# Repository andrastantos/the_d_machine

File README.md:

# tcomp
A transistor-based computer

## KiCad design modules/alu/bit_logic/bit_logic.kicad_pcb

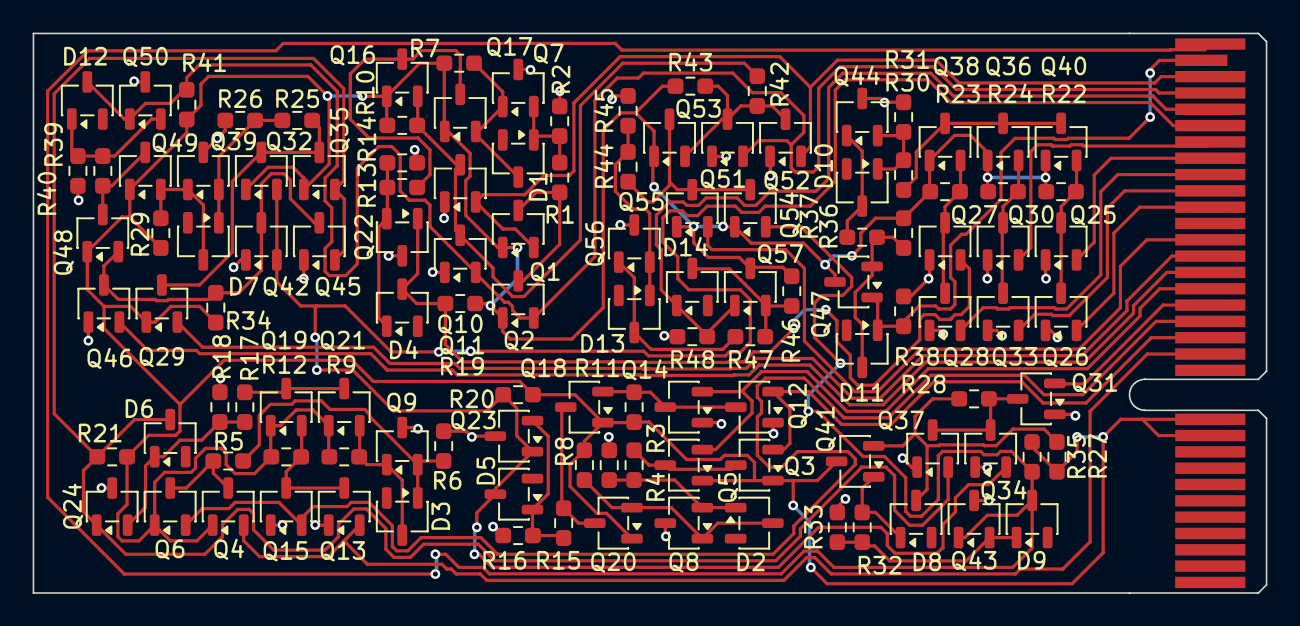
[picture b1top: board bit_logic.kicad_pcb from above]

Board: 2 copper layers, 75.6 x 34.3 mm, 120 parts (0 on the bottom side), 63 nets.

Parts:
D1, D2, D3, D4, D5, D6, D7, D8, D9, D10, D11, D12, D13, D14: BAT54LT1G; SOT-23-3
J1: PCIe_4x_edge; BUS_PCIexpress_x4
Q1, Q2, Q3, Q4, Q5, Q6, Q7, Q8, Q9, Q16, Q17, Q18, Q19, Q20, Q21, Q22, Q23, Q24, Q29, Q32, Q35, Q36, Q38, Q39, Q40, Q43, Q44, Q48, Q49, Q50, Q53, Q54, Q55, Q56: 2N3904; SOT-23-3
Q10, Q11, Q12, Q13, Q14, Q15, Q25, Q26, Q27, Q28, Q30, Q31, Q33, Q34, Q37, Q41, Q42, Q45, Q46, Q47, Q51, Q52, Q57: 2N3906; SOT-23-3
R1, R2, R3, R4, R5, R6, R13, R14, R15, R16, R17, R18, R25, R26, R27, R28, R30, R31, R39, R40, R44, R45: 220; R_0603_1608Metric_Pad0.98x0.95mm_HandSolder
R7, R8, R9, R19, R20, R21, R29, R32, R33, R35, R36, R37, R38, R41, R46, R47, R48: 100; R_0603_1608Metric_Pad0.98x0.95mm_HandSolder
R10, R11, R12, R22, R23, R24, R34, R43: 520; R_0603_1608Metric_Pad0.98x0.95mm_HandSolder
R42: 0; R_0603_1608Metric_Pad0.98x0.95mm_HandSolder

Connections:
/IN_A: J1.B14 (Pin_b14), Q3.2 (B), Q12.2 (B)
/IN_ADD_EN: J1.B24 (Pin_b24), Q28.2 (B)
/IN_AND_EN: J1.B19 (Pin_b19), Q29.2 (B)
/IN_A_NEXT: J1.B26 (Pin_b26), Q30.2 (B)
/IN_A_PREV: J1.B25 (Pin_b25), Q25.2 (B)
/IN_B: J1.B13 (Pin_b13), Q4.2 (B), Q13.2 (B)
/IN_C: J1.B30 (Pin_b30), Q1.2 (B), Q10.2 (B), Q52.2 (B)
/IN_C_IS_1: J1.B20 (Pin_b20), Q55.2 (B)
/IN_INV_A: J1.B17 (Pin_b17), Q5.2 (B), Q14.2 (B)
/IN_INV_B: J1.B15 (Pin_b15), Q6.2 (B), Q15.2 (B)
/IN_ROL_EN: J1.B22 (Pin_b22), Q26.2 (B)
/IN_ROR_EN: J1.B23 (Pin_b23), Q33.2 (B)
/OUT_A: D5.3 (K), J1.B27 (Pin_b27), Q23.1 (C), Q32.2 (B), Q34.2 (B), Q42.2 (B), R20.2
/OUT_C: D14.1 (A), J1.B28 (Pin_b28), Q57.1 (C), R48.1
/OUT_G: D9.3 (K), J1.B32 (Pin_b32), Q43.1 (C), Q54.2 (B), R35.2
/OUT_P: D12.3 (K), J1.B29 (Pin_b29), Q2.2 (B), Q11.2 (B), Q50.1 (C), Q51.2 (B), R41.2
/OUT_S: D11.1 (A), J1.B31 (Pin_b31), Q47.1 (C), R38.1
/XX: Q10.3 (E), Q11.3 (E), Q16.2 (B), R10.2, R42.1
/~IN_C_IS_0: J1.B16 (Pin_b16), Q31.2 (B)
/~IN_OR_EN: J1.B18 (Pin_b18), Q46.2 (B)
GND: J1.A10 (Pin_a10), J1.A11 (Pin_a11), J1.A12 (Pin_a12), J1.A13 (Pin_a13), J1.A14 (Pin_a14), J1.A15 (Pin_a15), J1.A16 (Pin_a16), J1.A17 (Pin_a17), J1.A18 (Pin_a18), J1.A19 (Pin_a19), J1.A20 (Pin_a20), J1.A21 (Pin_a21), J1.A22 (Pin_a22), J1.A23 (Pin_a23), J1.A24 (Pin_a24), J1.A25 (Pin_a25), J1.A26 (Pin_a26), J1.A27 (Pin_a27), J1.A28 (Pin_a28), J1.A29 (Pin_a29), J1.A30 (Pin_a30), J1.A31 (Pin_a31), J1.A32 (Pin_a32), Q7.3 (E), Q8.3 (E), Q9.3 (E), Q10.1 (C), Q11.1 (C), Q12.1 (C), Q13.1 (C), Q14.1 (C), Q15.1 (C), Q22.3 (E), Q23.3 (E), Q24.3 (E), Q25.1 (C), Q26.1 (C), Q27.1 (C), Q28.1 (C), Q30.1 (C), Q31.1 (C), Q33.1 (C), Q34.1 (C), Q37.1 (C), Q39.3 (E), Q42.1 (C), Q43.3 (E), Q44.3 (E), Q45.1 (C), Q46.1 (C), Q50.3 (E), Q51.1 (C), Q52.1 (C), Q56.3 (E), R2.2, R4.2, R6.2, R14.2, R16.2, R18.2, R26.2, R31.2, R33.2, R38.2, R40.2, R45.2, R48.2
unnamed: D1.1 (A), Q7.2 (B), R1.2, R2.1
unnamed: D1.3 (K), Q7.1 (C), Q17.2 (B), R7.2
unnamed: D2.1 (A), Q8.2 (B), R3.2, R4.1
unnamed: D2.3 (K), Q8.1 (C), Q20.2 (B), R8.2
unnamed: D3.1 (A), Q9.2 (B), R5.2, R6.1
unnamed: D3.3 (K), Q9.1 (C), Q21.2 (B), R9.2
unnamed: D4.1 (A), Q22.2 (B), R13.2, R14.1
unnamed: D4.3 (K), Q22.1 (C), Q27.2 (B), R19.2
unnamed: D5.1 (A), Q23.2 (B), R15.2, R16.1
unnamed: D6.1 (A), Q24.2 (B), R17.2, R18.1
unnamed: D6.3 (K), Q24.1 (C), Q35.2 (B), Q37.2 (B), Q45.2 (B), R21.2
unnamed: D7.1 (A), Q39.2 (B), R25.2, R26.1
unnamed: D7.3 (K), Q39.1 (C), Q49.2 (B), R29.2
unnamed: D8.1 (A), Q41.1 (C), R32.1
unnamed: D8.3 (K), Q41.2 (B), R27.2, R28.1
unnamed: D9.1 (A), Q43.2 (B), R32.2, R33.1
unnamed: D10.1 (A), Q44.2 (B), R30.2, R31.1
unnamed: D10.3 (K), Q44.1 (C), R37.2
unnamed: D11.3 (K), Q47.2 (B), R36.2, R37.1
unnamed: D12.1 (A), Q50.2 (B), R39.2, R40.1
unnamed: D13.1 (A), Q56.2 (B), R44.2, R45.1
unnamed: D13.3 (K), Q56.1 (C), R47.2
unnamed: D14.3 (K), Q57.2 (B), R46.2, R47.1
unnamed: Q1.3 (E), Q2.3 (E), R1.1
unnamed: Q3.3 (E), Q5.3 (E), R3.1
unnamed: Q4.3 (E), Q6.3 (E), R5.1
unnamed: Q12.3 (E), Q14.3 (E), Q18.2 (B), R11.2
unnamed: Q13.3 (E), Q15.3 (E), Q19.2 (B), R12.2
unnamed: Q16.3 (E), Q17.3 (E), R13.1
unnamed: Q18.3 (E), Q20.3 (E), R15.1
unnamed: Q19.3 (E), Q21.3 (E), R17.1
unnamed: Q25.3 (E), Q26.3 (E), Q40.2 (B), R22.2
unnamed: Q27.3 (E), Q28.3 (E), Q38.2 (B), R23.2
unnamed: Q29.3 (E), Q32.3 (E), Q35.3 (E), R25.1
unnamed: Q30.3 (E), Q33.3 (E), Q36.2 (B), R24.2
unnamed: Q31.3 (E), Q34.3 (E), Q37.3 (E), R28.2
unnamed: Q36.3 (E), Q38.3 (E), Q40.3 (E), R30.1
unnamed: Q42.3 (E), Q45.3 (E), Q46.3 (E), Q48.2 (B), R34.2
unnamed: Q48.3 (E), Q49.3 (E), R39.1
unnamed: Q51.3 (E), Q52.3 (E), Q53.2 (B), R42.2, R43.2
unnamed: Q53.3 (E), Q54.3 (E), Q55.3 (E), R44.1
VCC: J1.B10 (Pin_b10), J1.B11 (Pin_b11), Q1.1 (C), Q2.1 (C), Q3.1 (C), Q4.1 (C), Q5.1 (C), Q6.1 (C), Q16.1 (C), Q17.1 (C), Q18.1 (C), Q19.1 (C), Q20.1 (C), Q21.1 (C), Q29.1 (C), Q32.1 (C), Q35.1 (C), Q36.1 (C), Q38.1 (C), Q40.1 (C), Q41.3 (E), Q47.3 (E), Q48.1 (C), Q49.1 (C), Q53.1 (C), Q54.1 (C), Q55.1 (C), Q57.3 (E), R7.1, R8.1, R9.1, R10.1, R11.1, R12.1, R19.1, R20.1, R21.1, R22.1, R23.1, R24.1, R27.1, R29.1, R34.1, R35.1, R36.1, R41.1, R43.1, R46.1

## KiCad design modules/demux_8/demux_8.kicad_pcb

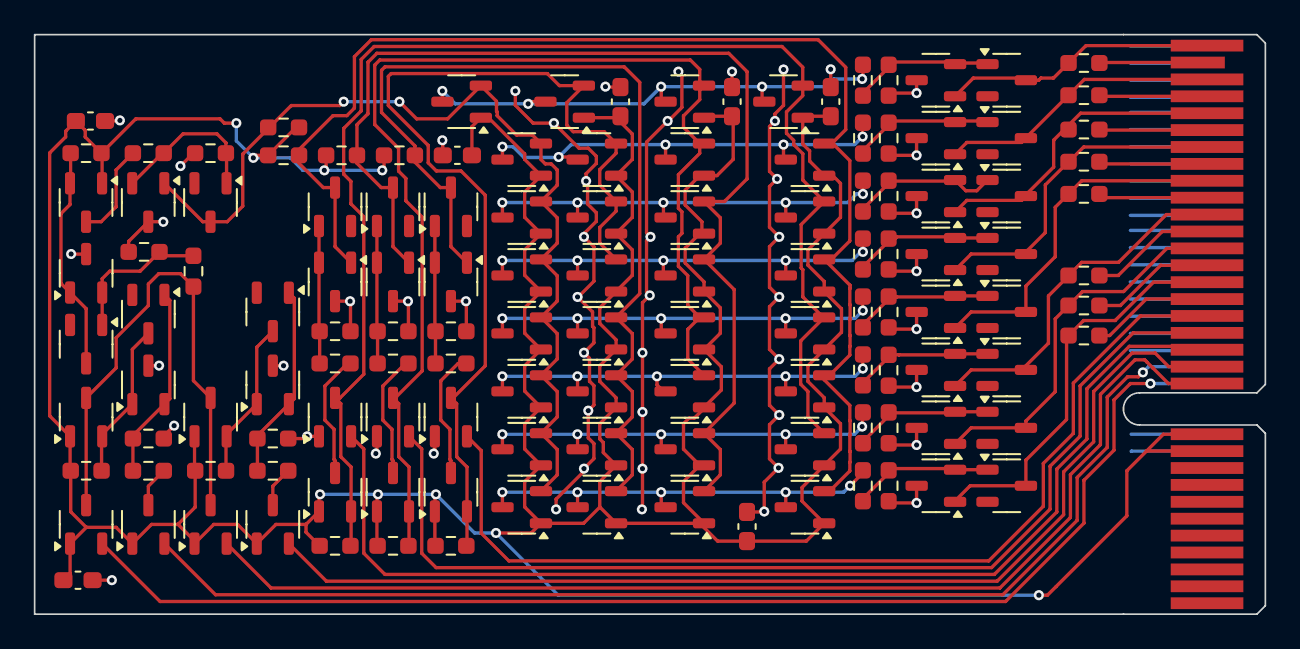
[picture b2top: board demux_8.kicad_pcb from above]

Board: 2 copper layers, 72.8 x 34.3 mm, 131 parts (0 on the bottom side), 65 nets.

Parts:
C1, C2, C3, C4, C5, C6, C7: 1u; C_0603_1608Metric_Pad1.08x0.95mm_HandSolder
D1, D2, D3, D4, D5, D6, D7, D8, D9, D10, D11, D12, D13, D14, D15: BAT54LT1G; SOT-23-3
J1: Conn_02x18_Row_Letter_First; BUS_PCIexpress_x4
Q1, Q5, Q6, Q7, Q8, Q9, Q10, Q11, Q12, Q13, Q14, Q15, Q16, Q17, Q18, Q19, Q20, Q21, Q22, Q23, Q24, Q25, Q26, Q27, Q28, Q29, Q30, Q31, Q32, Q33, Q34, Q35, Q36, Q37, Q38, Q39, Q40, Q41, Q42, Q43, Q44, Q45, Q46, Q47, Q48, Q49, Q50, Q51, Q52, Q53, Q54, Q55, Q56, Q57, Q58, Q59, Q60: 2N3904; SOT-23-3
Q2, Q3, Q4: 2N3906; SOT-23-3
R9, R10, R14, R15, R16, R17, R18, R19, R21, R22, R27, R28, R30, R31, R32, R33, R34, R35, R39, R40, R41, R42, R45, R46, R47, R48, R51, R52, R53, R54: 220; R_0603_1608Metric_Pad0.98x0.95mm_HandSolder
R11, R12, R13: 520; R_0603_1608Metric_Pad0.98x0.95mm_HandSolder
R20, R23, R24, R25, R26, R29, R36, R37, R38, R43, R44, R49, R50, R55, R56: 100; R_0603_1608Metric_Pad0.98x0.95mm_HandSolder

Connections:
/A: J1.B14 (Pin_b14), Q2.2 (B)
/B: J1.B15 (Pin_b15), Q3.2 (B)
/C: J1.B16 (Pin_b16), Q4.2 (B)
/EN: D6.3 (K), Q24.1 (C), Q27.2 (B), R29.2
/EN2: J1.B13 (Pin_b13), Q1.2 (B)
/EN3: J1.A13 (Pin_a13), Q9.2 (B)
/O0: D7.3 (K), J1.B18 (Pin_b18), Q28.1 (C), R36.2
/O1: D8.3 (K), J1.B20 (Pin_b20), Q29.1 (C), R37.2
/O2: D10.3 (K), J1.B22 (Pin_b22), Q39.1 (C), R43.2
/O3: D11.3 (K), J1.B24 (Pin_b24), Q40.1 (C), R44.2
/O4: D12.3 (K), J1.B26 (Pin_b26), Q49.1 (C), R49.2
/O5: D13.3 (K), J1.B28 (Pin_b28), Q50.1 (C), R50.2
/O6: D14.3 (K), J1.B30 (Pin_b30), Q59.1 (C), R55.2
/O7: D15.3 (K), J1.B32 (Pin_b32), Q60.1 (C), R56.2
/V_O0: J1.B17 (Pin_b17), R36.1
/V_O1: J1.B19 (Pin_b19), R37.1
/V_O2: J1.B21 (Pin_b21), R43.1
/V_O3: J1.B23 (Pin_b23), R44.1
/V_O4: J1.B25 (Pin_b25), R49.1
/V_O5: J1.B27 (Pin_b27), R50.1
/V_O6: J1.B29 (Pin_b29), R55.1
/V_O7: J1.B31 (Pin_b31), R56.1
/_A: Q2.3 (E), Q5.2 (B), Q18.2 (B), Q32.2 (B), Q42.2 (B), Q52.2 (B), R11.2
/_B: Q3.3 (E), Q6.2 (B), Q33.2 (B), Q34.2 (B), Q53.2 (B), Q54.2 (B), R12.2
/_C: Q4.3 (E), Q7.2 (B), Q45.2 (B), Q46.2 (B), Q55.2 (B), Q56.2 (B), R13.2
/_~A: D2.3 (K), Q10.1 (C), Q17.2 (B), Q31.2 (B), Q41.2 (B), Q51.2 (B), R23.2
/_~B: D3.3 (K), Q11.1 (C), Q20.2 (B), Q21.2 (B), Q43.2 (B), Q44.2 (B), R24.2
/_~C: D4.3 (K), Q12.1 (C), Q22.2 (B), Q23.2 (B), Q35.2 (B), Q36.2 (B), R25.2
/~EN0: J1.B12 (Pin_b12), Q14.2 (B)
/~EN1: J1.A12 (Pin_a12), Q15.2 (B)
/~EN: D9.3 (K), Q25.2 (B), Q26.2 (B), Q30.1 (C), Q37.2 (B), Q38.2 (B), Q47.2 (B), Q48.2 (B), Q57.2 (B), Q58.2 (B), R38.2
GND: C1.2, C2.2, C3.2, C4.2, C5.2, C6.2, C7.2, J1.A10 (Pin_a10), J1.A11 (Pin_a11), J1.A14 (Pin_a14), J1.A15 (Pin_a15), J1.A16 (Pin_a16), J1.A17 (Pin_a17), J1.A18 (Pin_a18), J1.A19 (Pin_a19), J1.A20 (Pin_a20), J1.A21 (Pin_a21), J1.A22 (Pin_a22), J1.A23 (Pin_a23), J1.A24 (Pin_a24), J1.A25 (Pin_a25), J1.A26 (Pin_a26), J1.A27 (Pin_a27), J1.A28 (Pin_a28), J1.A29 (Pin_a29), J1.A30 (Pin_a30), J1.A31 (Pin_a31), J1.A32 (Pin_a32), Q2.1 (C), Q3.1 (C), Q4.1 (C), Q8.3 (E), Q10.3 (E), Q11.3 (E), Q12.3 (E), Q13.3 (E), Q24.3 (E), Q28.3 (E), Q29.3 (E), Q30.3 (E), Q39.3 (E), Q40.3 (E), Q49.3 (E), Q50.3 (E), Q59.3 (E), Q60.3 (E), R10.2, R15.2, R17.2, R19.2, R22.2, R28.2, R31.2, R33.2, R35.2, R40.2, R42.2, R46.2, R48.2, R52.2, R54.2
unnamed: D1.1 (A), Q8.2 (B), R9.2, R10.1
unnamed: D1.3 (K), Q8.1 (C), Q16.2 (B), R20.2
unnamed: D2.1 (A), Q10.2 (B), R14.2, R15.1
unnamed: D3.1 (A), Q11.2 (B), R16.2, R17.1
unnamed: D4.1 (A), Q12.2 (B), R18.2, R19.1
unnamed: D5.1 (A), Q13.2 (B), R21.2, R22.1
unnamed: D5.3 (K), Q13.1 (C), Q19.2 (B), R26.2
unnamed: D6.1 (A), Q24.2 (B), R27.2, R28.1
unnamed: D7.1 (A), Q28.2 (B), R30.2, R31.1
unnamed: D8.1 (A), Q29.2 (B), R32.2, R33.1
unnamed: D9.1 (A), Q30.2 (B), R34.2, R35.1
unnamed: D10.1 (A), Q39.2 (B), R39.2, R40.1
unnamed: D11.1 (A), Q40.2 (B), R41.2, R42.1
unnamed: D12.1 (A), Q49.2 (B), R45.2, R46.1
unnamed: D13.1 (A), Q50.2 (B), R47.2, R48.1
unnamed: D14.1 (A), Q59.2 (B), R51.2, R52.1
unnamed: D15.1 (A), Q60.2 (B), R53.2, R54.1
unnamed: Q1.3 (E), R9.1
unnamed: Q5.3 (E), R14.1
unnamed: Q6.3 (E), R16.1
unnamed: Q7.3 (E), R18.1
unnamed: Q9.3 (E), R21.1
unnamed: Q14.3 (E), Q15.3 (E), Q16.3 (E), Q19.3 (E), R27.1
unnamed: Q17.3 (E), Q20.3 (E), Q22.3 (E), Q25.3 (E), R30.1
unnamed: Q18.3 (E), Q21.3 (E), Q23.3 (E), Q26.3 (E), R32.1
unnamed: Q27.3 (E), R34.1
unnamed: Q31.3 (E), Q33.3 (E), Q35.3 (E), Q37.3 (E), R39.1
unnamed: Q32.3 (E), Q34.3 (E), Q36.3 (E), Q38.3 (E), R41.1
unnamed: Q41.3 (E), Q43.3 (E), Q45.3 (E), Q47.3 (E), R45.1
unnamed: Q42.3 (E), Q44.3 (E), Q46.3 (E), Q48.3 (E), R47.1
unnamed: Q51.3 (E), Q53.3 (E), Q55.3 (E), Q57.3 (E), R51.1
unnamed: Q52.3 (E), Q54.3 (E), Q56.3 (E), Q58.3 (E), R53.1
VCC: C1.1, C2.1, C3.1, C4.1, C5.1, C6.1, C7.1, J1.B10 (Pin_b10), J1.B11 (Pin_b11), Q1.1 (C), Q5.1 (C), Q6.1 (C), Q7.1 (C), Q9.1 (C), Q14.1 (C), Q15.1 (C), Q16.1 (C), Q17.1 (C), Q18.1 (C), Q19.1 (C), Q20.1 (C), Q21.1 (C), Q22.1 (C), Q23.1 (C), Q25.1 (C), Q26.1 (C), Q27.1 (C), Q31.1 (C), Q32.1 (C), Q33.1 (C), Q34.1 (C), Q35.1 (C), Q36.1 (C), Q37.1 (C), Q38.1 (C), Q41.1 (C), Q42.1 (C), Q43.1 (C), Q44.1 (C), Q45.1 (C), Q46.1 (C), Q47.1 (C), Q48.1 (C), Q51.1 (C), Q52.1 (C), Q53.1 (C), Q54.1 (C), Q55.1 (C), Q56.1 (C), Q57.1 (C), Q58.1 (C), R11.1, R12.1, R13.1, R20.1, R23.1, R24.1, R25.1, R26.1, R29.1, R38.1

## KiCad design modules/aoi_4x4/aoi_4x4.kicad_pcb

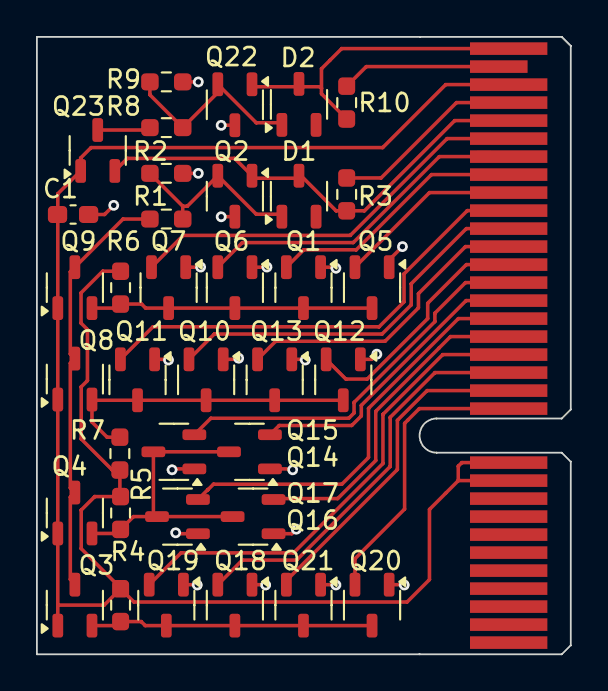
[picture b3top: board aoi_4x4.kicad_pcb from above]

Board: 2 copper layers, 29.7 x 34.3 mm, 37 parts (0 on the bottom side), 30 nets.

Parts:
C1: 1u; C_0603_1608Metric_Pad1.08x0.95mm_HandSolder
D1, D2: BAT54LT1G; SOT-23-3
J1: Conn_02x18_Row_Letter_First; BUS_PCIexpress_x4
Q1, Q5, Q6, Q7, Q10, Q11, Q12, Q13, Q14, Q15, Q16, Q17, Q18, Q19, Q20, Q21: 2N3906; SOT-23-3
Q2, Q3, Q4, Q8, Q9, Q22, Q23: 2N3904; SOT-23-3
R1, R2, R8, R9: 220; R_0603_1608Metric_Pad0.98x0.95mm_HandSolder
R3, R10: 100; R_0603_1608Metric_Pad0.98x0.95mm_HandSolder
R4, R5, R6, R7: 520; R_0603_1608Metric_Pad0.98x0.95mm_HandSolder

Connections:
/A: Q1.3 (E), Q5.3 (E), Q6.3 (E), Q7.3 (E), Q9.2 (B), R6.2
/B: Q8.2 (B), Q10.3 (E), Q11.3 (E), Q12.3 (E), Q13.3 (E), R7.2
/C: Q4.2 (B), Q14.3 (E), Q15.3 (E), Q16.3 (E), Q17.3 (E), R5.2
/D: Q3.2 (B), Q18.3 (E), Q19.3 (E), Q20.3 (E), Q21.3 (E), R4.2
/IN_A1: J1.B26 (Pin_b26), Q6.2 (B)
/IN_A2: J1.B27 (Pin_b27), Q7.2 (B)
/IN_A3: J1.B24 (Pin_b24), Q5.2 (B)
/IN_A4: J1.B25 (Pin_b25), Q1.2 (B)
/IN_B1: J1.B22 (Pin_b22), Q10.2 (B)
/IN_B2: J1.B23 (Pin_b23), Q11.2 (B)
/IN_B3: J1.B20 (Pin_b20), Q12.2 (B)
/IN_B4: J1.B21 (Pin_b21), Q13.2 (B)
/IN_C1: J1.B18 (Pin_b18), Q14.2 (B)
/IN_C2: J1.B19 (Pin_b19), Q15.2 (B)
/IN_C3: J1.B16 (Pin_b16), Q16.2 (B)
/IN_C4: J1.B17 (Pin_b17), Q17.2 (B)
/IN_D1: J1.B14 (Pin_b14), Q18.2 (B)
/IN_D2: J1.B15 (Pin_b15), Q19.2 (B)
/IN_D3: J1.B12 (Pin_b12), Q20.2 (B)
/IN_D4: J1.B13 (Pin_b13), Q21.2 (B)
/OUT: D2.3 (K), J1.B32 (Pin_b32), Q22.1 (C), R10.2
/V_OUT: J1.B31 (Pin_b31), R10.1
/V_~OUT: J1.B29 (Pin_b29), R3.1
/X: Q3.3 (E), Q4.3 (E), Q8.3 (E), Q9.3 (E), R1.1
/X2: D1.1 (A), Q2.2 (B), R1.2, R2.1
/Y: Q23.3 (E), R8.1
/Y2: D2.1 (A), Q22.2 (B), R8.2, R9.1
/~OUT: D1.3 (K), J1.B28 (Pin_b28), Q2.1 (C), Q23.2 (B), R3.2
GND: C1.2, J1.A10 (Pin_a10), J1.A11 (Pin_a11), J1.A12 (Pin_a12), J1.A13 (Pin_a13), J1.A14 (Pin_a14), J1.A15 (Pin_a15), J1.A16 (Pin_a16), J1.A17 (Pin_a17), J1.A18 (Pin_a18), J1.A19 (Pin_a19), J1.A20 (Pin_a20), J1.A21 (Pin_a21), J1.A22 (Pin_a22), J1.A23 (Pin_a23), J1.A24 (Pin_a24), J1.A25 (Pin_a25), J1.A26 (Pin_a26), J1.A27 (Pin_a27), J1.A28 (Pin_a28), J1.A29 (Pin_a29), J1.A30 (Pin_a30), J1.A31 (Pin_a31), J1.A32 (Pin_a32), Q1.1 (C), Q2.3 (E), Q5.1 (C), Q6.1 (C), Q7.1 (C), Q10.1 (C), Q11.1 (C), Q12.1 (C), Q13.1 (C), Q14.1 (C), Q15.1 (C), Q16.1 (C), Q17.1 (C), Q18.1 (C), Q19.1 (C), Q20.1 (C), Q21.1 (C), Q22.3 (E), R2.2, R9.2
VCC: C1.1, J1.B10 (Pin_b10), J1.B11 (Pin_b11), J1.B30 (Pin_b30), Q3.1 (C), Q4.1 (C), Q8.1 (C), Q9.1 (C), Q23.1 (C), R4.1, R5.1, R6.1, R7.1

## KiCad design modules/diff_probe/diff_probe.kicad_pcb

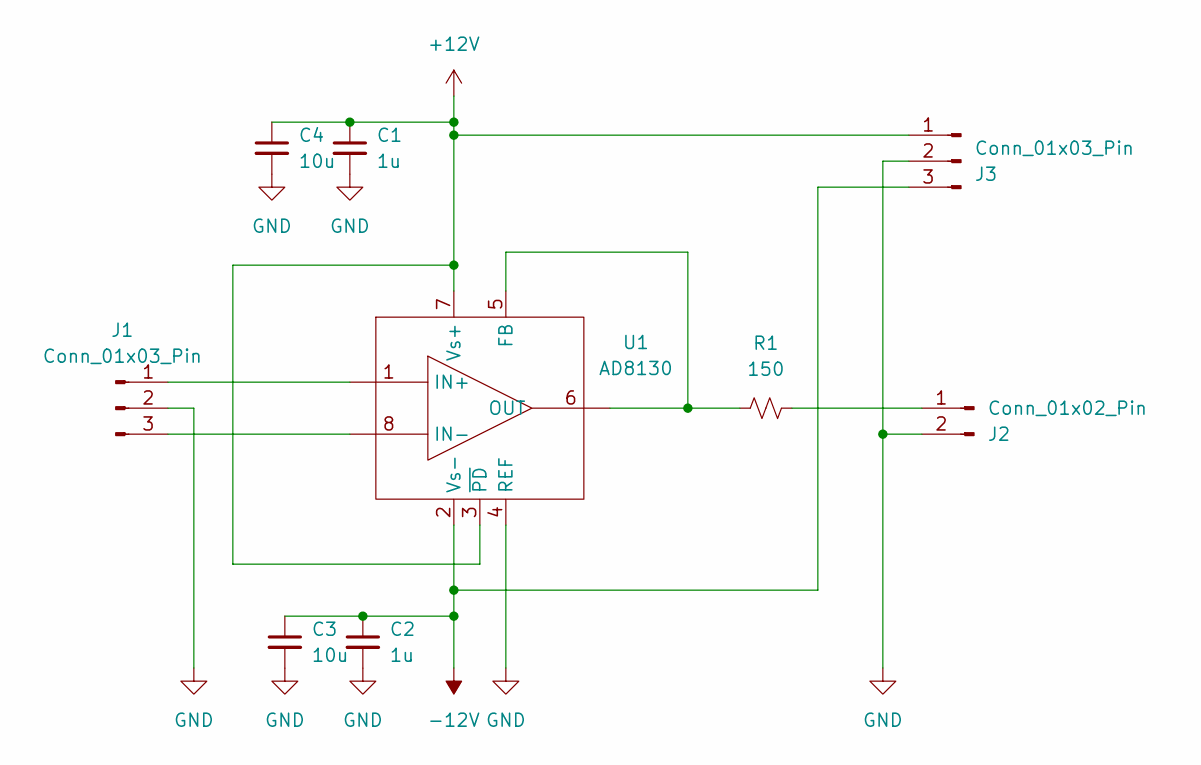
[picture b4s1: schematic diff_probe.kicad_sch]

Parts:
C1, C2: 1u; C_0603_1608Metric_Pad1.08x0.95mm_HandSolder
C3, C4: 10u; C_0805_2012Metric_Pad1.18x1.45mm_HandSolder
J1, J3: Conn_01x03_Pin; PinHeader_1x03_P2.54mm_Horizontal
J2: Conn_01x02_Pin; SMA_Amphenol_132289_EdgeMount
R1: 150; R_0603_1608Metric_Pad0.98x0.95mm_HandSolder
U1: AD8130; MSOP-8_3x3mm_P0.65mm

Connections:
+12V: C1.1, C4.1, J3.1, U1.3 (~PD), U1.7 (Vs+)
-12V: C2.1, C3.1, J3.3, U1.2 (Vs-)
GND: C1.2, C2.2, C3.2, C4.2, J1.2, J2.2, J3.2, U1.4 (REF)
unnamed: J1.1, U1.1 (IN+)
unnamed: J1.3, U1.8 (IN-)
unnamed: J2.1, R1.2
unnamed: R1.1, U1.5 (FB), U1.6 (OUT)

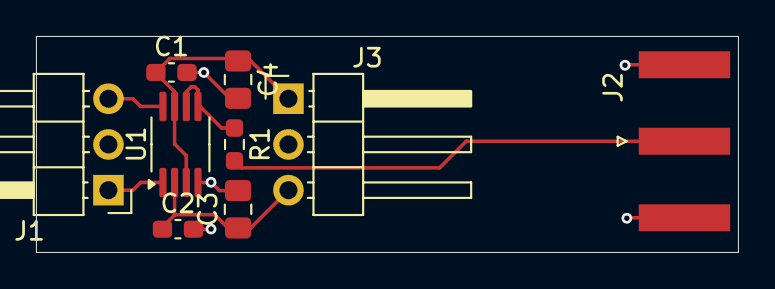
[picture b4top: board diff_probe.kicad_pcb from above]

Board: 2 copper layers, 39.0 x 12.0 mm, 9 parts (0 on the bottom side), 7 nets.

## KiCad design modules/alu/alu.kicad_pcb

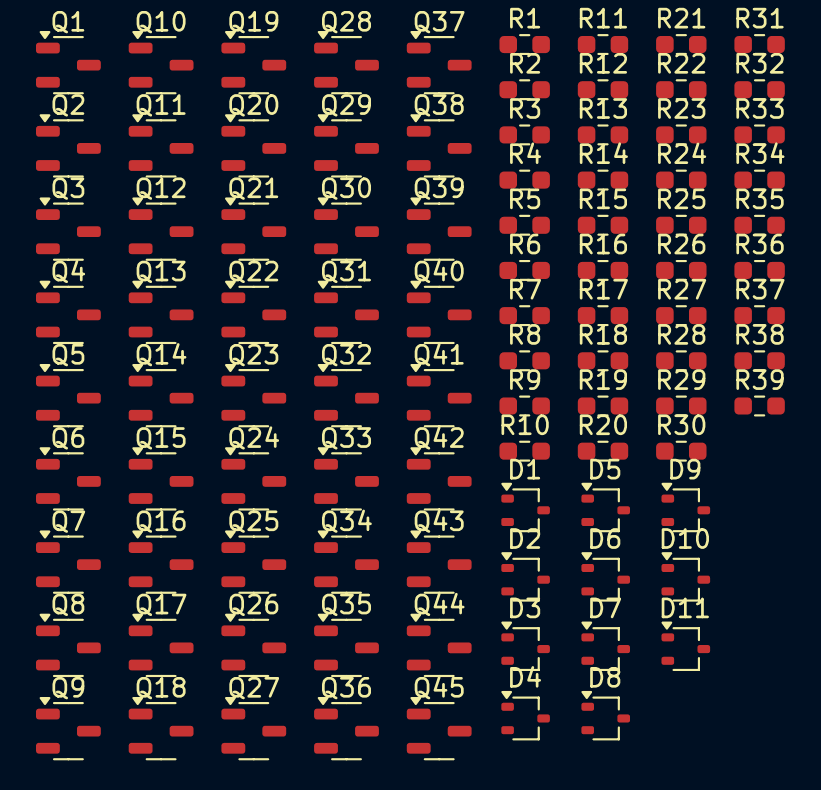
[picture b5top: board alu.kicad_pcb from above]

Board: 2 copper layers, 95 parts (0 on the bottom side), 44 nets, no tracks yet.

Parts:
D1, D2, D3, D4, D5, D6, D7, D8, D9, D10, D11: BAT54W; SOT-323_SC-70
Q1, Q2, Q3, Q4, Q5, Q6, Q11, Q12, Q13, Q14, Q15, Q16, Q17, Q19, Q21, Q23, Q28, Q29, Q30, Q33, Q34, Q36, Q43, Q44, Q45: 2N3904; SOT-23-3
Q7, Q8, Q9, Q10, Q18, Q20, Q22, Q24, Q25, Q26, Q27, Q31, Q32, Q35, Q37, Q38, Q39, Q40, Q41, Q42: 2N3906; SOT-23-3
R1, R2: 10k; R_0603_1608Metric_Pad0.98x0.95mm_HandSolder
R3, R4, R5, R6, R11, R12, R13, R14, R17, R18, R19, R20, R24, R25, R27, R28, R29, R30, R34, R35, R37, R38: 220; R_0603_1608Metric_Pad0.98x0.95mm_HandSolder
R7, R8, R15, R16, R21, R22, R26, R31, R32, R36, R39: 100; R_0603_1608Metric_Pad0.98x0.95mm_HandSolder
R9, R10, R23, R33: 520; R_0603_1608Metric_Pad0.98x0.95mm_HandSolder

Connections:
0: Q5.3 (E), Q6.3 (E), Q7.1 (C), Q8.1 (C), Q9.1 (C), Q10.1 (C), Q15.3 (E), Q16.3 (E), Q18.1 (C), Q20.1 (C), Q22.1 (C), Q23.3 (E), Q25.1 (C), Q26.1 (C), Q27.1 (C), Q30.3 (E), Q31.1 (C), Q32.1 (C), Q36.3 (E), Q37.1 (C), Q38.1 (C), Q39.1 (C), Q40.1 (C), Q41.1 (C), Q45.3 (E), R1.2, R2.2, R4.2, R6.2, R12.2, R14.2, R18.2, R22.2, R25.2, R30.2, R31.2, R36.2, R38.2
/A0: D3.3 (K), Q15.1 (C), Q19.2 (B), Q20.2 (B), Q25.2 (B), R15.2
/B0: D4.3 (K), Q16.1 (C), Q21.2 (B), Q22.2 (B), Q26.2 (B), R16.2
/IN_A0: Q1.2 (B), Q7.2 (B)
/IN_B0: Q2.2 (B), Q8.2 (B)
/IN_C0: Q31.2 (B), Q33.2 (B), Q39.2 (B)
/IN_INV_A: Q3.2 (B), Q9.2 (B), R1.1
/IN_INV_B: Q4.2 (B), Q10.2 (B), R2.1
/OUT_C1: D10.1 (A), Q42.1 (C), R36.1
/OUT_P0: D7.3 (K), Q30.1 (C), Q32.2 (B), Q34.2 (B), Q41.2 (B), R26.2
/OUT_S0: D11.3 (K), Q45.1 (C), R39.2
/~OUT_G0: D6.1 (A), Q24.1 (C), Q38.2 (B), R22.1
unnamed: D1.1 (A), Q5.2 (B), R3.2, R4.1
unnamed: D1.3 (K), Q5.1 (C), Q13.2 (B), R7.2
unnamed: D2.1 (A), Q6.2 (B), R5.2, R6.1
unnamed: D2.3 (K), Q6.1 (C), Q14.2 (B), R8.2
unnamed: D3.1 (A), Q15.2 (B), R11.2, R12.1
unnamed: D4.1 (A), Q16.2 (B), R13.2, R14.1
unnamed: D5.1 (A), Q23.2 (B), R17.2, R18.1
unnamed: D5.3 (K), Q23.1 (C), Q29.2 (B), R21.2
unnamed: D6.3 (K), Q24.2 (B), R19.2, R20.1
unnamed: D7.1 (A), Q30.2 (B), R24.2, R25.1
unnamed: D8.1 (A), Q35.1 (C), Q40.2 (B), R31.1
unnamed: D8.3 (K), Q35.2 (B), R27.2, R28.1
unnamed: D9.1 (A), Q36.2 (B), R29.2, R30.1
unnamed: D9.3 (K), Q36.1 (C), Q44.2 (B), R32.2
unnamed: D10.3 (K), Q42.2 (B), R34.2, R35.1
unnamed: D11.1 (A), Q45.2 (B), R37.2, R38.1
unnamed: Q1.3 (E), Q3.3 (E), R3.1
unnamed: Q2.3 (E), Q4.3 (E), R5.1
unnamed: Q8.3 (E), Q10.3 (E), Q12.2 (B), R10.2
unnamed: Q7.3 (E), Q9.3 (E), Q11.2 (B), R9.2
unnamed: Q11.3 (E), Q13.3 (E), R11.1
unnamed: Q12.3 (E), Q14.3 (E), R13.1
unnamed: Q17.3 (E), Q19.3 (E), Q21.3 (E), R17.1
unnamed: Q18.3 (E), Q20.3 (E), Q22.3 (E), R20.2
unnamed: Q25.3 (E), Q26.3 (E), Q27.3 (E), Q28.2 (B), R23.2
unnamed: Q28.3 (E), Q29.3 (E), R24.1
unnamed: Q31.3 (E), Q32.3 (E), R28.2
unnamed: Q33.3 (E), Q34.3 (E), R29.1
unnamed: Q37.3 (E), Q38.3 (E), Q40.3 (E), R35.2
unnamed: Q39.3 (E), Q41.3 (E), Q43.2 (B), R33.2
unnamed: Q43.3 (E), Q44.3 (E), R37.1
VCC: Q1.1 (C), Q2.1 (C), Q3.1 (C), Q4.1 (C), Q11.1 (C), Q12.1 (C), Q13.1 (C), Q14.1 (C), Q17.1 (C), Q19.1 (C), Q21.1 (C), Q24.3 (E), Q28.1 (C), Q29.1 (C), Q33.1 (C), Q34.1 (C), Q35.3 (E), Q42.3 (E), Q43.1 (C), Q44.1 (C), R7.1, R8.1, R9.1, R10.1, R15.1, R16.1, R19.1, R21.1, R23.1, R26.1, R27.1, R32.1, R33.1, R34.1, R39.1

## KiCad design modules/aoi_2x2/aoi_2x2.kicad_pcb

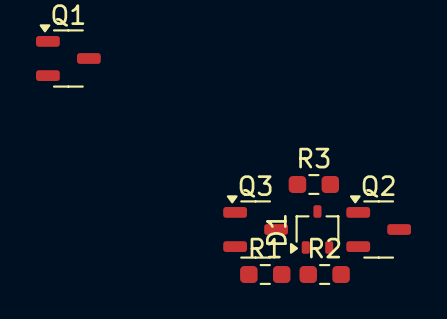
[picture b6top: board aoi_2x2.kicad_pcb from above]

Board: 2 copper layers, 7 parts (0 on the bottom side), 5 nets, no tracks yet.

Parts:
D1: BAT54W; SOT-323_SC-70
Q1: 2N3906; SOT-23-3
Q2, Q3: 2N3904; SOT-23-3
R1: 600; R_0603_1608Metric_Pad0.98x0.95mm_HandSolder
R2, R3: 300; R_0603_1608Metric_Pad0.98x0.95mm_HandSolder

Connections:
0: Q2.3 (E), R2.2
/BASE: D1.1 (A), Q2.2 (B), R1.2, R2.1
/OUT: D1.3 (K), Q2.1 (C), R3.2
unnamed: Q3.3 (E), R1.1
VCC: Q3.1 (C), R3.1

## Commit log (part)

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2025-04-27 Checking in initial work
2025-04-28 Some notes on how much savings a TTL implementation would get in cycle-time reduction.
2025-04-30 Started serious work on ALU
2025-04-30 Adder more or less completed.
    A few problems:
    - We have NOR and NAND instead of OR and AND
    - No SWAP support (if we want it)
2025-04-30 Attempt at a shift register.
    Right now the BJT version if fast, seems to work, but *very* expensive.
2025-05-02 Still not sure how to make a cheap, low-power and fast SRAM cell.
    No wonder it was difficult back then as well...
2025-05-05 Finally have a more or less functional bit-cell.
    Also logic gates are totally busted, they have massive shoot-through. How did I miss that?
2025-05-06 Finally, a working, fast, relatively low power and cheap inverter!
    On the other side of the ledger, this needs 3 power supplies.
2025-05-07 Finally figured out temperature compensation.
    This circuit now works well at 5V, though current consumption is high.
    I also need now 4 (!) power supplies, fine-tuned to compensate for Vbe drop.
    This is for now represented by ideal voltage supplies, but of course it
    will need to be something that needs to be implemented by
    real circuits in the end.
    But, at least it allows me to make forward progress.
2025-05-07 I don't think I can get a better bit-cell then this.
    Here we have a 5V, ~20ns, relatively low power bit-cell, where the two inverters and the shift-enable logic total needs only 6 transistors and 2 diodes. I'm not sure I would want to use the same desi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
    For things with parallel load requirements yet another structure (with 2 more transistors to make the input OR gates less hacky) might be needed. Or maybe not. We shall see.
2025-05-08 2-bit ALU test.
    This has a worst-case propagation delay of 120ns, just about fast enough for 8MHz. On the hairy edge, and if anything else slows things down, it won't make it.
    I think I'll have to find more complex and faster inverters if I want to make this thing tick...
2025-05-08 Fine-tuned ALU to work at 20MHz.
    This simply means reducing the input emitter-follower resistance (Rin) to 33ohms. NOTE: this is not the actual resistance, that is a multiple of this.
    At any rate, this results in 20MHz operation (~50ns propagation delay) for a 250mA power.
    I think I'll take this and move on...
2025-05-08 Sped up carry generation by adding an extra transistor.
2025-05-09 Well, the bit-cell is foo-bared. Lot's of work ahead.
2025-05-09 An attempt at a full shift-register. Doesn't quite work. Yet.
2025-05-09 Some attempt at a 10MHz version at least. Not cheese, but some progress.
2025-05-13 So, the only reasonable D-flop is the BJT one with a whopping 20T/4D design per bit.
    Even this, *even this*, only runs up to 10MHz over temperature. At least, it can be made faster by tuning the supply voltage, so if reality is less forgiving, it can be made to work still.
2025-05-14 Timing diagram added
2025-05-15 CPU code is more or less complete.
    I haven't even tried to compile let alone run it.
    Also, SWAP still doesn't work and the implementation
    is almost certainly rather boneheaded.
2025-05-16 Much more to ignore...
2025-05-16 Some signs of life, though I think there's now a Silicon bug I've found.
2025-05-19 Typo...
2025-05-19 MOV is a unary op now.
    Also fixed completely bonkers unary/binary/predicate selection logic.
2025-05-19 Updated documentation, musings on bit-banging I/O
2025-05-19 Updated wave file
2025-05-20 Visualization file rename
2025-05-22 A *way* more capable assembler.
    This supports symbols, expressions, sections, pseudo-ops, multi-line
    assembly. It is even capable of generating binary for a trivial single-line
    source.
2025-05-23 Some minor fix to simulator.
2025-05-25 Fixed some assembly and memory dump issues.
2025-05-28 Basic confidence test is complete and passing.
    Including memory content comparison.
2025-05-29 Much progress towards fixing RTL bugs.
    Not quite there yet, but the BCT test does wonders in rooting out bugs.
2025-05-29 Started bit-slice implementation.
    This is untested and more or less a direct port of the LTSpice model.
2025-05-31 Some progress with gate-level ALU.
    Add/sub seems to work, NOR doesn't.
2025-06-01 Some further ALU optimization.
    Now the ROL/ROR chains are tied off of already existing inverters.
2025-06-01 Some more gate-ification.
2025-06-02 One-hot encoded phases.
2025-06-03 Replaced ALU input selects and BUS commands with individual wires.
    At least on the interface level. Sequencer still uses the enums
    internally to figure out what ALU input to drive to what.
2025-06-03 Gate-ification of opa_select
2025-06-09 Fixed (but not tested) interrupt handling.
    The fix is to allow ISWAP to increment $PC after
    execution, thus allowing for the skipping of the
    return from interrupt instruction. This makes
    setting the interrupt vector a bit awkward, but
    oh, well.
2025-06-10 Added another latch to really fix interrupt handling.
    That is: the ISWAP executed during interrupt
    handling should *NOT* increment the
    stored $PC. Since, upon returning from
    the interrupt handler, we want to retry
    the interrupted instruction.
2025-06-11 Removed a mux branch and updated diagrams.
    By moving the loading of L_BUS_D to phase 4, we don't ever have a need
    for loading it from L_ALU_RESULT. This is a nice savings even if
    the control of the loading in phase 4 is now a bit more complicated.
2025-06-12 Added whole computer block diagram.
2025-06-13 Added latch simulation
2025-06-16 Some documentation updates.
2025-06-18 Full 16-bit ALU out of transistors.
    The propagation delay seems to be pretty
    good, actually:
    ~220ns at 125C and (thought the sim is still running)
    ~350ns at -25C
    This is well within target for 400ns and
    kind of surprising for a ripple-carry
2025-06-19 Small ALU fix.
2025-06-22 Removed all instances of 'Select' from Sequencer.
    This is needed, because
    a) we don't actually need them
    b) we don't have a transistor count estimation for them.
2025-06-24 Moved carry generation into ALU bit-cell.
2025-06-30 A workable sense-amp design.
    This can probably be fine-tuned a little to
    get for instance power consumption
    under control, but otherwise, pretty
    good.
    The design is DC-coupled.
    It has about 85ns delay to it, but I don't
2025-07-07 Created a semi-decent current-source
2025-07-07 DEC version of the current source.
2025-07-08 New current sense amp.
2025-07-09 Added driver IC datasheet that DEC used.
2025-07-10 More work on switches
2025-07-11 Some cleanup of the BJT line driver.
    It still doesn't work BTW.
2025-07-11 Started work on sense-inhibit.
    This is much harder then I thought. Oh, well...
2025-07-14 I can't make a current source, apparently.
2025-07-16 Fantastic! This circuit isn't even stable with inductive loads.
    I've added some dampers to keep that in check,
    but now it's sluggish, especially in ring-down.
    So, hopefully, I won't have a really inductive load.
    Actually all indication is that I won't.
2025-07-18 OK, git is weird. Anyway, I think I can accept this version.
    It overshoots, but stable and I more or
    less convinced myself that the overshoot
    is safe.
2025-07-22 Deep dive into core memories.
2025-07-24 Started some documentation
2025-08-20 Some more analysis on fast inverters.
    There is maybe some way of balancing power
    consumption and speed. But it's not
    pretty.
2025-08-22 New line-switch driver idea.
2025-08-25 Some progress towards an inhibit switch.
2025-08-26 Fine-tuned step-response.
    Now we have ~100ns rise-times and
    a 50ns turn-on delay.
2025-08-28 I finally understand what the problem with the bride is.
    Essentially, the top-side inactive FET Cgs needs to be charged up because the
    bridge is powered by a current source
    that varies the top voltage whilst the gate
    is held at a constant voltage.
    How to fix this though is a different
    animal all together.
2025-08-29 I think - apart from the input delays - load driver is done.
    I need to find a way to skinny up the low-side
    drive by about 50ns on both sides. Other
    that that though, it seems things are
    working relatively well. Fingers crossed...
2025-08-29 Some beautification for the article.
2025-09-23 Test bed for current switches
2025-10-02 Dunno, some changes, it seems adding a 2-ohm resistor for some reason.
2025-10-29 Added fancy level-shifters to the H-bridge.
    This is getting ugly fast: 11-12 transistors PER power transistor.
    That's more than 2000 transistors just for the X-Y driver circuit.
    With inhibit drivers, we're around 2500 transistors.
2025-11-03 Created complementer high-side drive. Now the shoot-through is gone.
    This is even crazier than the previous design:
    now all power transistor are of the wrong kind.
    In other words, all power BJTs are in an emitter
    follower configuration. This also has much
    worse step-response, probably because the
    missing shoot-through doesn't "pre-charge"
2025-11-07 Created some drawings for the timing circuit.
2025-11-07 I now have a couple of oscillating oscillators.
    I'm not quite sure if I wanted to use them:
    it seems a major PITA to get them logic level
    compliant.
2025-11-13 Added (somewhat different, but still very relevant) Yamaha manual
2025-11-14 Pretty good progress on a ROM sense amplifier.
    The positive feedback idea is a really good one to get high sensitivity and reasonable speed.
2025-11-25 Spent a lot of time with common-base input stages.
    Not sure I got to where I want to be, but there is *something*. About 150uV output swing with
    a significantly larger temperature-dependent offset (even though the circuit is now pretty well
    temperature compensated). It's also rather complicated at 5 transistors. I'm wondering though
    if the emitter followers are needed, or if the common-base input can drive the diff-amp directly...
2025-11-26 Some work on standardizing component values and reducing power consumption.
    The detector still works, but the detection is slow, so the threshold is pulse-width
    dependent.
2025-12-03 Some musings about how diff-amps work. Or should work.
    Right now, the diff amp is nice, the sense-amp has all sorts of non-idealities, plus it's more complex and less performant then the original one ripped from Motorola.
2025-12-10 Checking in diff probe and AOI module work.
2025-12-13 Tape sense amplifier more or less figured out.
2025-12-17 Some changes, probably to the cascode parts that are going to soon be irrelevant.
2025-12-18 Added power supply filters to increase PSRR.
2025-12-22 I have no clue what changed here. Checking it in anyway.
2025-12-26 Some work towards a functional PWM-modulated buck.
2025-12-30 Yet another buck trial.
2026-01-05 This (rather expensive) switch driver seems to work nicely.
    In fact, it's good enough with a PFET up to a few houndred kHz, probably.
2026-01-05 More probing and some stress-testing.
    The output depends quite a lot on the input supply, that is
    about 10% variation over 5-25V input range. Temperature
    as it stands at the moment has similar impact. The overshoot
    is still there and I'm not sure about load or supply regulation.
2026-01-06 Added soft-start circuit. I think the buck converter is done now.
2026-01-08 Finally the two transformer models agree.
2026-01-09 Some outstanding changes.
2026-01-13 Forward regulator (at least BJT-CMOS one) is more or less done.
2026-01-16 Linear regulators more or less done. Some experiments with coupling the boost voltage regulator output.
2026-01-24 Tuned some values to make the regulator more temperature-tolerant.
2026-01-27 Some cosmetic fixes to power-good detectors.
2026-01-28 Small finalizing changes to reset logic.
2026-01-30 Started working towards real modules. Modules with PCIe connectors.
2026-03-04 Started PCIe connector-based module design.
2026-03-09 Started 8-way decoder. It's ... large.
2026-04-25 Some fixes to the ALU schematics
2026-05-24 Notes about video (wait-state) support and protected mode.
2026-05-24 PCB is more or less done. It's DRC clean but needs bypass caps and some power optimizations.
2026-05-28 Final MMU block diagram,
2026-06-02 Added (totally untested) interrupt controller.
    Right now the corresponding interrupt sticky-bit from the MMU is NOT removed.
    I'll have to convince myself that it's safe to remove as the *OUTPUT* of the
    sticky bit is used within the MMU. So maybe the corresponding sticky-bit would
    need to be routed from the interrupt controller back? That sounds like a mess...
